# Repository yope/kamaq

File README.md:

Kamaq
=====

1. Introduction
---------------

Kamaq is a 3D-printer (FDM) controller software running on an embedded Linux
system. It is capable of controlling a RepRap-style 3D printer, but with
different electronics. Stepper motor control is done using a 8-channel (7.1)
USB audio device and some class-D audio amplifiers. Endstop switches are
monitored via GPIO inputs (interrupt-capable) and temperature control for
extruder and heated bed via standard hwmon-compatible ADC's and GPIO-outputs
for heater control. The software has a web-iterface for machine control and
monitoring. Why do it like this when there are already so many different hard-
and software projects dedicated to 3D printers (RepRap and all its
derivatives)?  Well, because as is the case with all engineers, I always know
better ;-)

2. Status of this project
-------------------------

This project is currently in heavy development. There are some bugs and missing
features, but overall the software can be (and has been) used for many
successful prints.
The software can control 4 motors (X, Y, Z and Extruder), read 3 endswitches
and control extruder- and heated-bed temperatures. The G-Code interpreter is
still very simple, but the software is already able to succesfully print
objects from a G-Code-file generated with cura or repsnapper.

3. Platform requirements
------------------------

Kamaq should be able to run on any embedded linux platform such as the beagle-
board, beagle-bone or the raspberry-pi with a suitable audio device, GPIO and
HWmon compatible A/D converters for temperature measurement.
The sound device should have twice the number of channels as the number of
motors that need to be controlled. For example a cheap 7.1 USB audio device
will be enough for controlling 4 stepper-motors.

4. Main application
-------------------

Of course the main goal for this project is controlling 3D-printer hardware,
such as the RepRap Prusa i3 for example, but it may also be adapted for other
applications requiring control of motors from G-Codes.

5. Required hardware
--------------------

5.1. Audio device
-----------------

The sound-card will work better if modified slightly, by shorting the DC-
blocking capacitors at the output. On many USB audio devices this is a
trivial task to do. For example the Sweex SC016 contains a C-Media CM6206
7.1 channel USB audio codec. Datasheets can easily be found via Google, and
they contain reference schematics that will be very similar to most
implementations of popular 7.1 USB audio devices that use this chip.
Most of the time they will use cheap through-hole electrolytic capacitors,
that are very easy to short out.

5.2. Audio amplifiers
---------------------

Bipolar 2-phase stepper-motors are best driven by a controlled current.
Although in theory, having a good model of the motor that takes into account
inductance and back-EMF at different speeds, one could calculate the correct
voltage-waveform to be applied to the motor windings and just use a voltage-
amplifier wich might be a little easier to build (specially when using class-D
amplifier IC's).
For my first hardware implementation, I built very simple class-B amplifiers
with current-feedback based on a bunch of TDA2030A I had laying around. This
version didn't require any motor modeling.
The second version which I am currently using is based on class-D audio
amplifier IC's, which save a lot of space and simplify the power supply
enormously. The class-D amplifiers lack current-feedback though, so I have
added rudimentary software support for voltage control also.

5.3. Heater control
-------------------

To control heater elements (such as for the extruder or the heated-bed of a
3D-printer), simple low-side switches with power-MOSFETS with very low-Rdson
will be perfect.
Temperature feedback is best implemented via simple A/D converters that support
HW-mon drivers, such as the ADS1015 from TI, which has mainline-linux support.

5.4. Hardware implementation
----------------------------

I have implemented all the needed hardware to control a 3D printer using this
software in very little time and effort. If there is enough interest I might
open-source the hardware (Kicad schematics and layout) too, but it is really
simple and straight-forward stuff right now hacked together in very little time.

6. Tools
--------

 * kamaq.py: Main application, starts the web-server.

 * grunner.py: This command-line tool can execude whole G-Code files or single
   movements by specifying relative distance on each axis (including extruder)
   on the command-line. It supports homing on endswitches and extruder
   temperature control. Currently not functional. Use the web-server instead.

 * set_current.py: Very simple tool that sets constant motor currents for all
   motors specified on the command-line. Can be used for adjusting motor
   current via the audio mixer. For each motor, two values are specified from
   -30000 to 30000, corresponding to the currents through each of the two
   coils. If less than 8 values (for 4 motors) are specified, the rest is
   assumed to be 0.

 * adjust_bed.sh: A script that aids in adjusting the for corners of the print-
   bed.

 * clean_extruder.sh: Move to a suitable position (high enough Z), heat
   extruder and start extruding a few cm. Deprecated. Will be removed soon
   probably.

7. TODO:
--------

Features that may or may not be implemented in the near or far future:

 * Implement pause and resume-from-layer-X.
 * Implemet G-code control via SSH or Serial port (to be able to use traditional
   printer control software).

8. Building Kamaq:
------------------

Install build dependencies (debian jessie or ubuntu):

 $ sudo apt-get install python3 cython3 libasound2-dev

Building (in-place, installation not supported yet):

 $ make

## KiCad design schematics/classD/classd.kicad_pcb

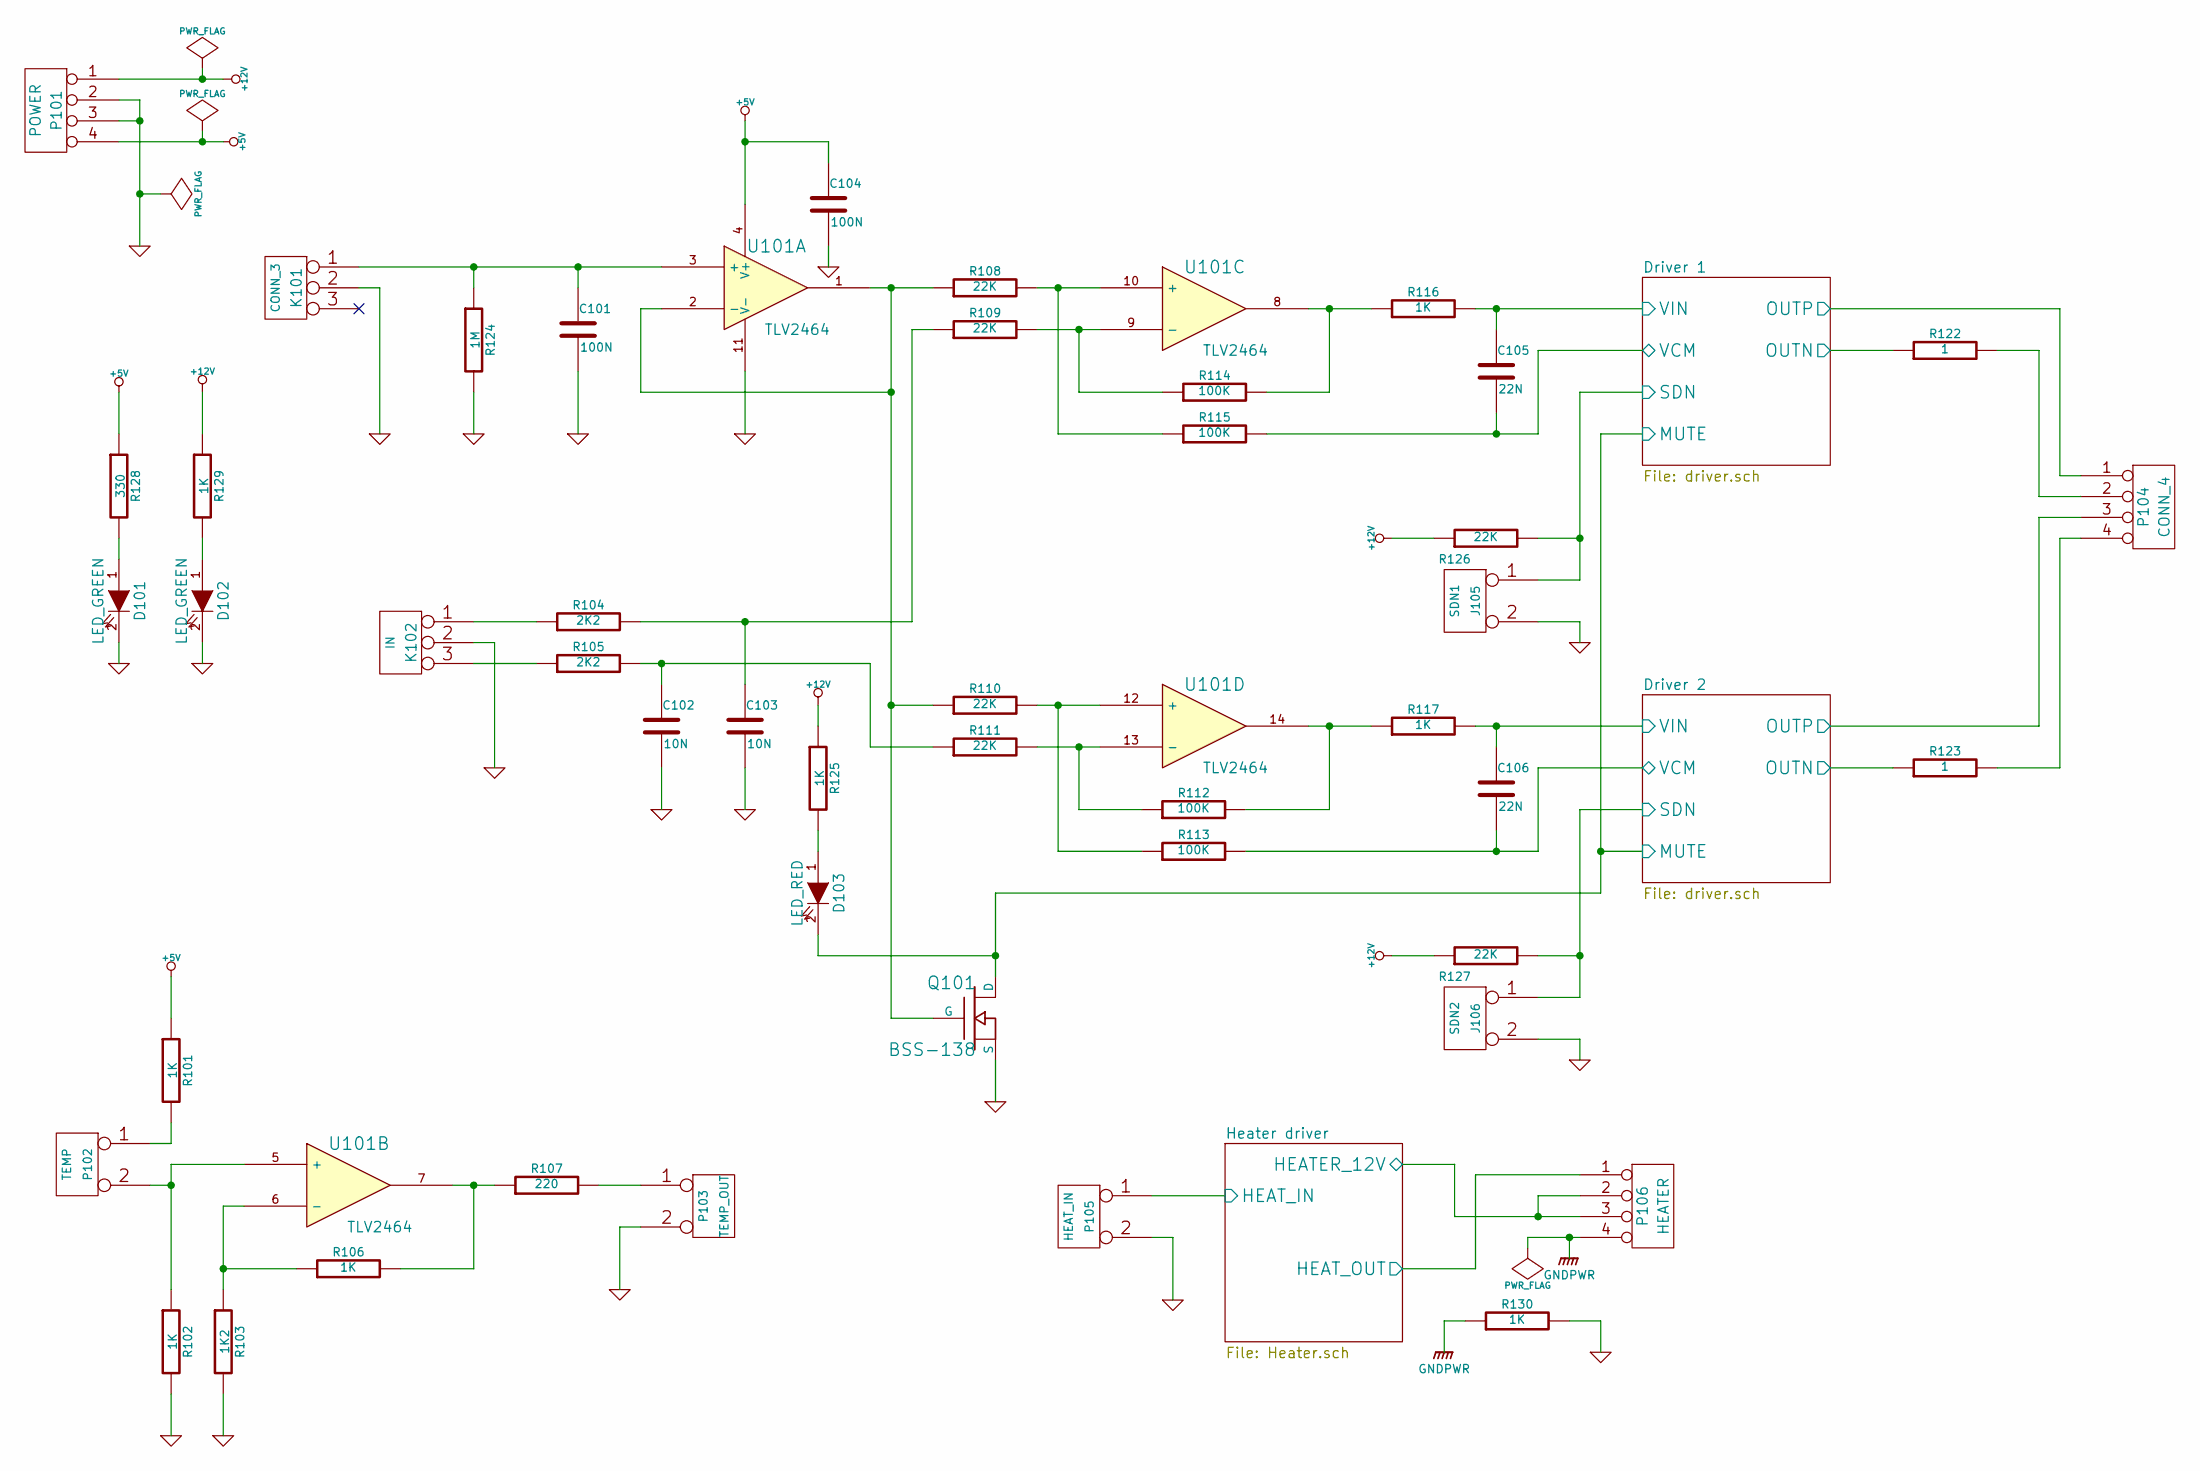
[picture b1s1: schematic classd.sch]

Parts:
C101, C104: 100N
C102, C103: 10N
C105, C106: 22N
D101, D102: LED_GREEN
D103: LED_RED
J105: SDN1
J106: SDN2
K101: CONN_3
K102: IN
P101: POWER
P102: TEMP
P103: TEMP_OUT
P104: CONN_4
P105: HEAT_IN
P106: HEATER
Q101: BSS-138
R101, R102, R106, R116, R117, R125, R129, R130: 1K
R103: 1K2
R104, R105: 2K2
R107: 220
R108, R109, R110, R111, R126, R127: 22K
R112, R113, R114, R115: 100K
R122, R123: 1
R124: 1M
R128: 330
U101: TLV2464

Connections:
+5V: C104.1, P101.4, R101.1, R128.1, U101.4 (V+); also elsewhere on the board
+12V: P101.1, R125.1, R126.1, R127.1, R129.1; also elsewhere on the board
/Driver 1/MUTE: D103.2 (K), Q101.D; also elsewhere on the board
/Driver 1/OUTN: R122.1; also elsewhere on the board
/Driver 1/OUTP: P104.1; also elsewhere on the board
/Driver 1/SDN: J105.1, R126.2; also elsewhere on the board
/Driver 1/VCM: C105.2, R115.2; also elsewhere on the board
/Driver 1/VIN: C105.1, R116.2; also elsewhere on the board
/Driver 2/OUTN: R123.1; also elsewhere on the board
/Driver 2/OUTP: P104.3; also elsewhere on the board
/Driver 2/SDN: J106.1, R127.2; also elsewhere on the board
/Driver 2/VCM: C106.2, R113.2; also elsewhere on the board
/Driver 2/VIN: C106.1, R117.2; also elsewhere on the board
/Heater driver/HEATER_12V: P106.2, P106.3; also elsewhere on the board
/Heater driver/HEAT_IN: P105.1; also elsewhere on the board
/Heater driver/HEAT_OUT: P106.1; also elsewhere on the board
GND: C101.2, C102.2, C103.2, C104.2, D101.2 (K), D102.2 (K), J105.2 (PM), J106.2 (PM), K101.2 (PM), K102.2 (PM), P101.2, P101.3, P103.2 (PM), P105.2 (PM), Q101.S, R102.2, R103.2, R124.2, R130.2, U101.11 (V-); also elsewhere on the board
GNDPWR: P106.4, R130.1; also elsewhere on the board
unnamed: P102.2 (PM), R102.1, U101.5 (+)
unnamed: P103.1, R107.2
unnamed: R106.2, R107.1, U101.7
unnamed: R103.1, R106.1, U101.6 (-)
unnamed: P102.1, R101.2
unnamed: D101.1 (A), R128.2
unnamed: D102.1 (A), R129.2
unnamed: D103.1 (A), R125.2
unnamed: R114.2, R116.1, U101.8
unnamed: Q101.G, R108.1, R110.1, U101.1, U101.2 (-)
unnamed: R109.2, R114.1, U101.9 (-)
unnamed: C103.1, R104.2, R109.1
unnamed: R108.2, R115.1, U101.10 (+)
unnamed: P104.4, R123.2
unnamed: P104.2, R122.2
unnamed: K102.3, R105.1
unnamed: C102.1, R105.2, R111.1
unnamed: K102.1, R104.1
unnamed: C101.1, K101.1, R124.1, U101.3 (+)
unnamed: R112.2, R117.1, U101.14
unnamed: R110.2, R113.1, U101.12 (+)
unnamed: R111.2, R112.1, U101.13 (-)

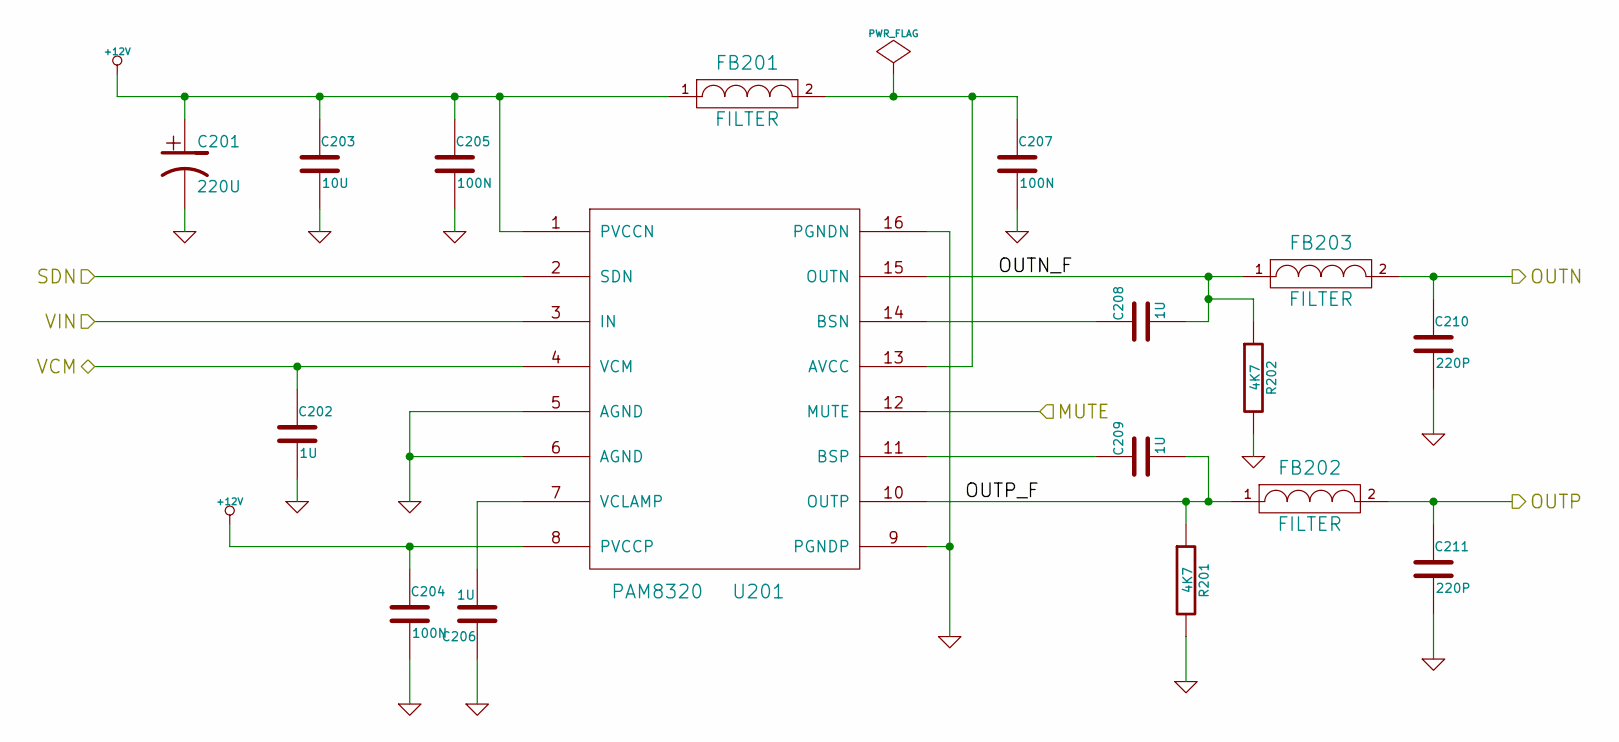
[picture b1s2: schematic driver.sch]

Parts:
C201: 220U
C202, C206, C208, C209: 1U
C203: 10U
C204, C205, C207: 100N
C210, C211: 220P
FB201, FB202, FB203: FILTER
R201, R202: 4K7
U201: PAM8320

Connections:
+12V: C201.1, C203.1, C204.1, C205.1, FB201.1, U201.1 (PVCCN), U201.8 (PVCCP); also elsewhere on the board
/Driver 1/MUTE: U201.12 (MUTE); also elsewhere on the board
/Driver 1/OUTN: C210.1, FB203.2; also elsewhere on the board
/Driver 1/OUTN_F: C208.2, FB203.1, R202.1, U201.15 (OUTN)
/Driver 1/OUTP: C211.1, FB202.2; also elsewhere on the board
/Driver 1/OUTP_F: C209.2, FB202.1, R201.1, U201.10 (OUTP)
/Driver 1/SDN: U201.2 (SDN); also elsewhere on the board
/Driver 1/VCM: C202.1, U201.4 (VCM); also elsewhere on the board
/Driver 1/VIN: U201.3 (IN); also elsewhere on the board
GND: C201.2, C202.2, C203.2, C204.2, C205.2, C206.1, C207.2, C210.2, C211.2, R201.2, R202.2, U201.5 (AGND), U201.6 (AGND), U201.9 (PGNDP), U201.16 (PGNDN); also elsewhere on the board
unnamed: C206.2, U201.7 (VCLAMP)
unnamed: C207.1, FB201.2, U201.13 (AVCC)
unnamed: C209.1, U201.11 (BSP)
unnamed: C208.1, U201.14 (BSN)

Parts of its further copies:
C301: 220U
C302, C306, C308, C309: 1U
C303: 10U
C304, C305, C307: 100N
C310, C311: 220P
FB301, FB302, FB303: FILTER
R301, R302: 4K7
U301: PAM8320

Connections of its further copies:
+12V: C301.1, C303.1, C304.1, C305.1, FB301.1, U301.1 (PVCCN), U301.8 (PVCCP); also elsewhere on the board
/Driver 1/MUTE: U301.12 (MUTE); also elsewhere on the board
/Driver 2/OUTN: C310.1, FB303.2; also elsewhere on the board
/Driver 2/OUTN_F: C308.2, FB303.1, R302.1, U301.15 (OUTN)
/Driver 2/OUTP: C311.1, FB302.2; also elsewhere on the board
/Driver 2/OUTP_F: C309.2, FB302.1, R301.1, U301.10 (OUTP)
/Driver 2/SDN: U301.2 (SDN); also elsewhere on the board
/Driver 2/VCM: C302.1, U301.4 (VCM); also elsewhere on the board
/Driver 2/VIN: U301.3 (IN); also elsewhere on the board
GND: C301.2, C302.2, C303.2, C304.2, C305.2, C306.1, C307.2, C310.2, C311.2, R301.2, R302.2, U301.5 (AGND), U301.6 (AGND), U301.9 (PGNDP), U301.16 (PGNDN); also elsewhere on the board
unnamed: C306.2, U301.7 (VCLAMP)
unnamed: C307.1, FB301.2, U301.13 (AVCC)
unnamed: C309.1, U301.11 (BSP)
unnamed: C308.1, U301.14 (BSN)

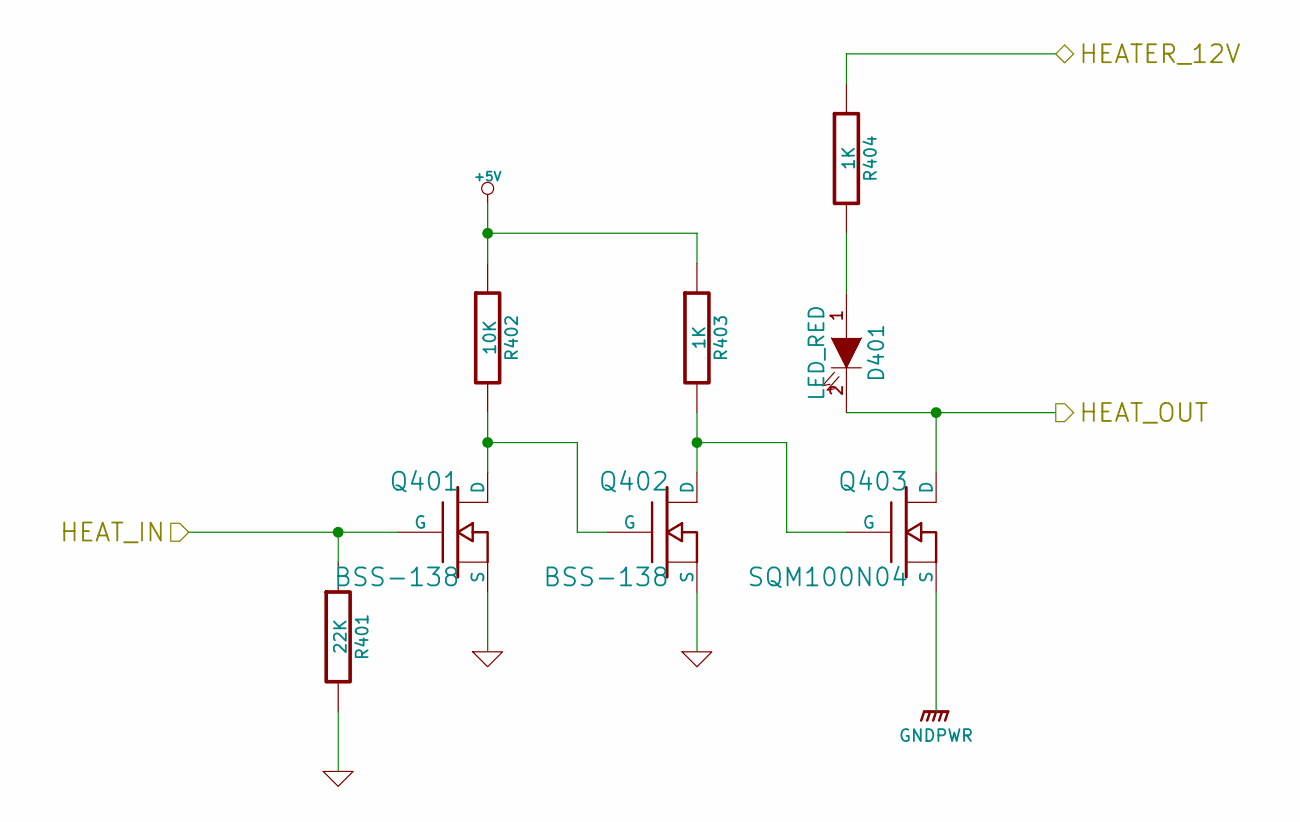
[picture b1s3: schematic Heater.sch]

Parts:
D401: LED_RED
Q401, Q402: BSS-138
Q403: SQM100N04
R401: 22K
R402: 10K
R403, R404: 1K

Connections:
+5V: R402.1, R403.1; also elsewhere on the board
/Heater driver/HEATER_12V: R404.1; also elsewhere on the board
/Heater driver/HEAT_IN: Q401.G, R401.1; also elsewhere on the board
/Heater driver/HEAT_OUT: D401.2 (K), Q403.2 (D); also elsewhere on the board
GND: Q401.S, Q402.S, R401.2; also elsewhere on the board
GNDPWR: Q403.3 (S); also elsewhere on the board
unnamed: Q402.D, Q403.1 (G), R403.2
unnamed: Q401.D, Q402.G, R402.2
unnamed: D401.1 (A), R404.2

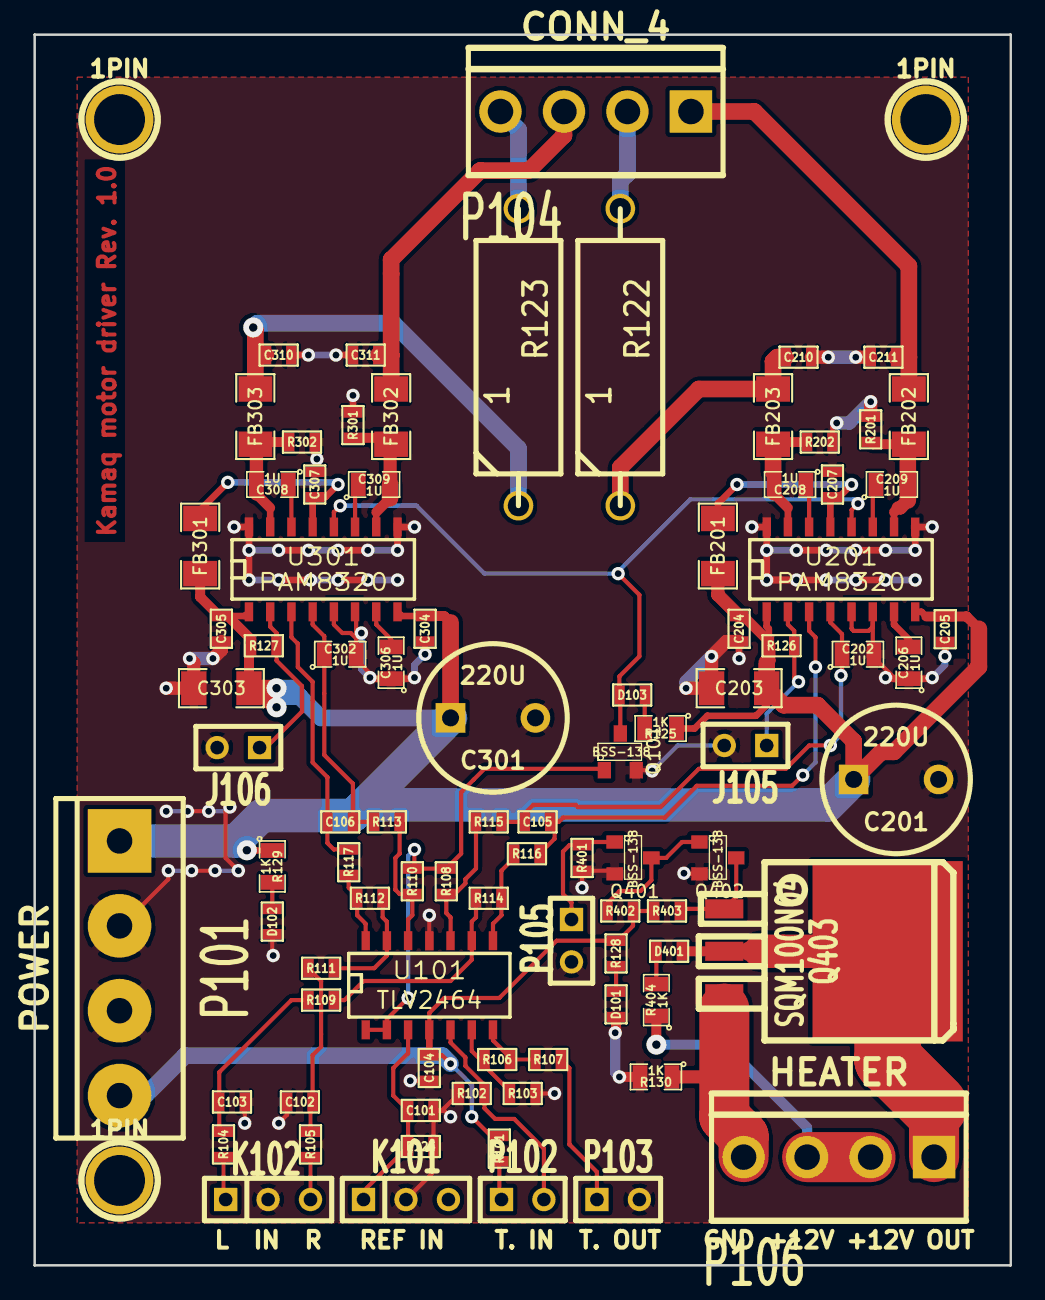
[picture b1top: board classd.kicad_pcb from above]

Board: 2 copper layers, 58.4 x 73.7 mm, 92 parts (0 on the bottom side), 55 nets.

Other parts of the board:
1PIN, 1PIN#2, 1PIN#3: P***; 1pin

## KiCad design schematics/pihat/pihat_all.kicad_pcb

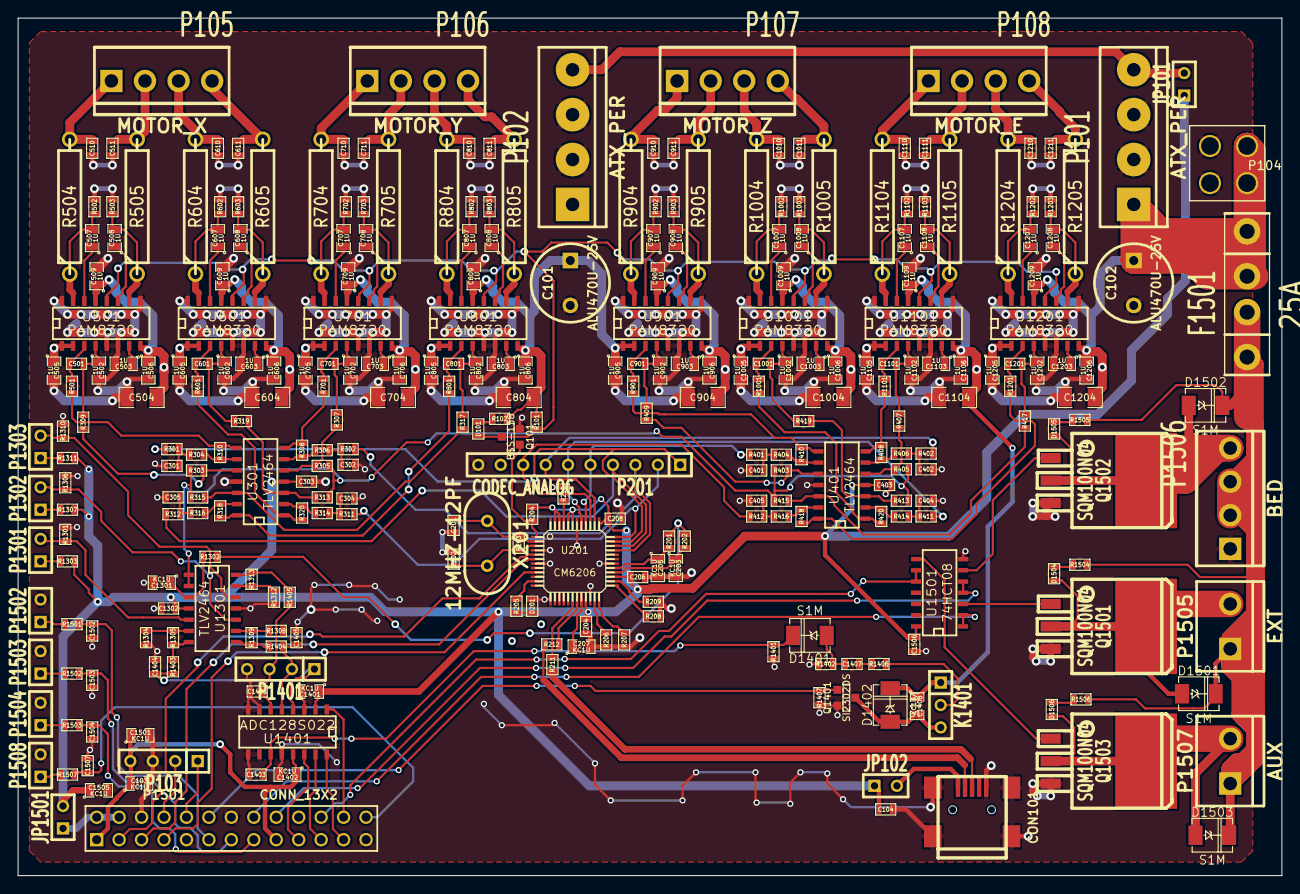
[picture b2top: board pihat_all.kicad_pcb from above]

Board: 2 copper layers, 143.0 x 97.0 mm, 305 parts (0 on the bottom side), 192 nets.

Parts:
C101, C102: ALU470U-25V; C2V8
C103, C203, C205, C207, C1301, C1401, C1402, C1408, C1501, C1505: KC1U; SM0805
C104: KC10U; SM0603
C201, C202, C204, C206, C208, C303, C403, C1302, C1403, C1502, C1503, C1504, C1506, C1507: 100N; SM0603
C301, C302, C304, C305, C401, C402, C404, C405, C501, C601, C701, C801, C901, C1001, C1101, C1201, C1404, C1405, C1406, C1407: 10N; SM0603
C502, C503, C505, C506, C507, C508, C509, C602, C603, C605, C606, C607, C608, C609, C702, C703, C705, C706, C707, C708, C709, C802, C803, C805, C806, C807, C808, C809, C902, C903, C905, C906, C907, C908, C909, C1002, C1003, C1005, C1006, C1007, C1008, C1009, C1102, C1103, C1105, C1106, C1107, C1108, C1109, C1202, C1203, C1205, C1206, C1207, C1208, C1209: 1U; SM0805
C504, C604, C704, C804, C904, C1004, C1104, C1204: 10U; SM1206
C510, C511, C610, C611, C710, C711, C810, C811, C910, C911, C1010, C1011, C1110, C1111, C1210, C1211: 220P; SM0603
CON101: USB-MINI-B; USB_MINI_B
D101, D201, D1504, D1505, D1506: LED; SM0603
D1401, D1402, D1501, D1502, D1503: S1M; DO-214AC(SMA)
F1501: 25A; ATO257
JP101, JP102, JP1501: JUMPER; SIL-2
K1401: FAN; SIL-3
P101, P102: ATX_PER; bornier4
P103: SERIAL; SIL-4
P104: MOLEX-39-28-1043; MINIFIT-4
P105: MOTOR_X; MC4
P106: MOTOR_Y; MC4
P107: MOTOR_Z; MC4
P108: MOTOR_E; MC4
P201: CODEC_ANALOG; SIL-10
P1301: TEMP_EXT; SIL-2
P1302: TEMP_BED; SIL-2
P1303: TEMP_AUX; SIL-2
P1401: TEMP_ADC; SIL-4
P1501: CONN_13X2; pin_array_13x2
P1502: END_X; SIL-2
P1503: END_Y; SIL-2
P1504: END_Z; SIL-2
P1505: EXT; bornier2
P1506: BED; MC4
P1507: AUX; bornier2
P1508: END_L; SIL-2
Q101: BSS-138; SOT23GDS
Q1401: SI2302DS; SOT23GDS
Q1501, Q1502, Q1503: SQM100N04; TO263
R101, R102, R1301, R1302, R1303, R1305, R1306, R1307, R1309, R1310, R1311, R1313, R1402, R1406, R1501, R1502, R1503, R1504, R1505, R1506, R1507: 1K; SM0603
R201: N.P.; SM0603
R202: 0; SM0603
R203: 1M; SM0603
R204, R303, R304, R305, R306, R313, R314, R315, R316, R403, R404, R405, R406, R413, R414, R415, R416, R1401, R1407: 22K; SM0603
R205: 330; SM0603
R206, R207, R208, R209, R210, R307, R308, R309, R310, R317, R318, R319, R320, R407, R408, R409, R410, R417, R418, R419, R420: 10K; SM0603
R211, R212: 22; SM0603
R301, R302, R311, R312, R401, R402, R411, R412, R501, R601, R701, R801, R901, R1001, R1101, R1201: 2.2K; SM0603
R502, R503, R602, R603, R702, R703, R802, R803, R902, R903, R1002, R1003, R1102, R1103, R1202, R1203: 47K; SM0603
R504, R505, R604, R605, R704, R705, R804, R805, R904, R905, R1004, R1005, R1104, R1105, R1204, R1205: 0.5/3W; R6
R1304, R1308, R1312: 1.2K; SM0603
R1403, R1404, R1405: 47; SM0603
U201: CM6206; AB2_LQFP48
U301, U401, U1301: TLV2464; SO14E
U501, U601, U701, U801, U901, U1001, U1101, U1201: PAM8320; SO16E
U1401: ADC128S022; SO16E
U1501: 74HCT08; SO14E
X201: 12MHZ-12PF; HC-49V

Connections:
+3.3V: C103.1, C1402.1, C1501.1, P103.4, P1501.1, P1501.17, U1401.13
+5V: C104.1, C204.1, C206.1, C208.1, C303.1, C403.1, C1302.1, C1401.1, C1505.1, C1506.1, JP101.1, JP102.1, JP1501.2, R204.1, R1303.1, R1307.1, R1311.1, U201.21, U201.27, U201.37, U201.43, U201.44, U201.46, U201.47, U301.4, U401.4, U1301.4, U1401.2, U1501.14
+12V: C101.1, C102.1, C504.1, C505.1, C506.1, C509.1, C604.1, C605.1, C606.1, C609.1, C704.1, C705.1, C706.1, C709.1, C804.1, C805.1, C806.1, C809.1, C904.1, C905.1, C906.1, C909.1, C1004.1, C1005.1, C1006.1, C1009.1, C1104.1, C1105.1, C1106.1, C1109.1, C1204.1, C1205.1, C1206.1, C1209.1, C1408.1, D1402.2, F1501.1, K1401.1, P101.1, P102.1, P104.3, P104.4, R101.1, R102.1, U501.1, U501.2, U501.8, U501.13, U601.1, U601.2, U601.8, U601.13, U701.1, U701.2, U701.8, U701.13, U801.1, U801.2, U801.8, U801.13, U901.1, U901.2, U901.8, U901.13, U1001.1, U1001.2, U1001.8, U1001.13, U1101.1, U1101.2, U1101.8, U1101.13, U1201.1, U1201.2, U1201.8, U1201.13
/ADC/FAN_PWM: P1501.12, Q1401.G, R1407.1
/ADC/SPI_MISO: P1501.21, U1401.15
/ADC/SPI_MOSI: P1501.19, U1401.14
/ADC/SPI_SCLK: P1501.23, U1401.16
/ADC/TEMP_AUX: R1313.2, R1405.2, U1301.14
/ADC/TEMP_BED: R1309.2, R1404.2, U1301.8
/ADC/TEMP_EXT: R1305.2, R1403.2, U1301.7
/Audio Codec/CODEC_VBIAS: C205.1, R201.2, U201.29
/Audio Codec/CODEC_VREF: C203.1, R202.2, U201.28
/Audio Codec/MINT: P1501.7, U201.9
/Audio Codec/PDSW: Q101.G, R204.2, U201.1
/Audio Codec/SCL: P1501.5, U201.6
/Audio Codec/SDA: P1501.3, U201.5
/Audio Codec/USB_DM: CON101.2, R212.1
/Audio Codec/USB_DP: CON101.3, R211.1
/Audio Codec/VBIAS: R201.1, R202.1, R1302.1
/Biasing1/IN_A: P201.1, R301.1, U201.35
/Biasing1/IN_B: P201.2, R311.1, U201.36
/Biasing1/IN_C: P201.3, R302.1, U201.33
/Biasing1/IN_D: P201.4, R312.1, U201.34
/Biasing2/IN_A: P201.5, R401.1, U201.40
/Biasing2/IN_B: P201.6, R411.1, U201.41
/Biasing2/IN_C: P201.7, R402.1, U201.38
/Biasing2/IN_D: P201.8, R412.1, U201.39
/GPIO/GPIO7: C1507.1, P1501.26, R1507.1
/GPIO/GPIO17: C1502.1, P1501.11, R1501.1
/GPIO/GPIO22: C1504.1, P1501.15, R1503.1
/GPIO/GPIO23: P1501.16, U1501.1, U1501.2
/GPIO/GPIO24: P1501.18, U1501.4, U1501.5
/GPIO/GPIO25: P1501.22, U1501.9, U1501.10
/GPIO/GPIO27: C1503.1, P1501.13, R1502.1
/GPIO/SPI_nCE0: P1501.24, U1401.1
/GPIO/UART_RXD: P103.1, P1501.10
/GPIO/UART_TXD: P103.2, P1501.8
/Power Amp 1/OUTN: C510.1, P105.1, R504.2
/Power Amp 1/OUTP: C511.1, P105.2, R505.2
/Power Amp 1/VCM: C501.2, C502.1, R309.2, U501.4
/Power Amp 1/VIN: R310.2, R501.1, U301.8
/Power Amp 2/OUTN: C610.1, P105.3, R604.2
/Power Amp 2/OUTP: C611.1, P105.4, R605.2
/Power Amp 2/VCM: C601.2, C602.1, R319.2, U601.4
/Power Amp 2/VIN: R320.2, R601.1, U301.1
/Power Amp 3/OUTN: C710.1, P106.1, R704.2
/Power Amp 3/OUTP: C711.1, P106.2, R705.2
/Power Amp 3/VCM: C701.2, C702.1, R307.2, U701.4
/Power Amp 3/VIN: R308.2, R701.1, U301.7
/Power Amp 4/OUTN: C810.1, P106.3, R804.2
/Power Amp 4/OUTP: C811.1, P106.4, R805.2
/Power Amp 4/VCM: C801.2, C802.1, R317.2, U801.4
/Power Amp 4/VIN: R318.2, R801.1, U301.14
/Power Amp 5/OUTN: C910.1, P107.1, R904.2
/Power Amp 5/OUTP: C911.1, P107.2, R905.2
/Power Amp 5/VCM: C901.2, C902.1, R409.2, U901.4
/Power Amp 5/VIN: R410.2, R901.1, U401.8
/Power Amp 6/OUTN: C1010.1, P107.3, R1004.2
/Power Amp 6/OUTP: C1011.1, P107.4, R1005.2
/Power Amp 6/VCM: C1001.2, C1002.1, R419.2, U1001.4
/Power Amp 6/VIN: R420.2, R1001.1, U401.1
/Power Amp 7/OUTN: C1110.1, P108.1, R1104.2
/Power Amp 7/OUTP: C1111.1, P108.2, R1105.2
/Power Amp 7/VCM: C1101.2, C1102.1, R407.2, U1101.4
/Power Amp 7/VIN: R408.2, R1101.1, U401.7
/Power Amp 8/OUTN: C1210.1, P108.3, R1204.2
/Power Amp 8/OUTP: C1211.1, P108.4, R1205.2
/Power Amp 8/VCM: C1201.2, C1202.1, R417.2, U1201.4
/Power Amp 8/VIN: R418.2, R1201.1, U401.14
GND: C101.2, C102.2, C103.2, C104.2, C201.2, C202.2, C203.2, C204.2, C205.2, C206.2, C207.2, C208.2, C301.2, C302.2, C303.2, C304.2, C305.2, C401.2, C402.2, C403.2, C404.2, C405.2, C502.2, C503.2, C504.2, C505.2, C506.2, C509.2, C510.2, C511.2, C602.2, C603.2, C604.2, C605.2, C606.2, C609.2, C610.2, C611.2, C702.2, C703.2, C704.2, C705.2, C706.2, C709.2, C710.2, C711.2, C802.2, C803.2, C804.2, C805.2, C806.2, C809.2, C810.2, C811.2, C902.2, C903.2, C904.2, C905.2, C906.2, C909.2, C910.2, C911.2, C1002.2, C1003.2, C1004.2, C1005.2, C1006.2, C1009.2, C1010.2, C1011.2, C1102.2, C1103.2, C1104.2, C1105.2, C1106.2, C1109.2, C1110.2, C1111.2, C1202.2, C1203.2, C1204.2, C1205.2, C1206.2, C1209.2, C1210.2, C1211.2, C1301.2, C1302.2, C1401.2, C1402.2, C1403.2, C1404.2, C1405.2, C1406.2, C1501.2, C1502.2, C1503.2, C1504.2, C1505.2, C1506.2, C1507.2, CON101.5, CON101.6, CON101.7, CON101.8, CON101.9, D201.2, P101.2, P101.3, P102.2, P102.3, P103.3, P104.1, P104.2, P201.10, P1401.4, P1501.6, P1501.9, P1501.14, P1501.20, P1501.25, P1502.2, P1503.2, P1504.2, P1506.1, P1508.2, Q101.S, Q1401.S, Q1501.3, Q1502.3, Q1503.3, R206.2, R207.2, R208.2, R209.2, R210.2, R502.2, R503.2, R602.2, R603.2, R702.2, R703.2, R802.2, R803.2, R902.2, R903.2, R1002.2, R1003.2, R1102.2, R1103.2, R1202.2, R1203.2, R1301.2, R1304.2, R1306.2, R1308.2, R1310.2, R1312.2, R1401.1, R1402.2, R1407.2, U201.4, U201.7, U201.13, U201.22, U201.30, U201.42, U301.11, U401.11, U501.5, U501.6, U501.9, U501.16, U601.5, U601.6, U601.9, U601.16, U701.5, U701.6, U701.9, U701.16, U801.5, U801.6, U801.9, U801.16, U901.5, U901.6, U901.9, U901.16, U1001.5, U1001.6, U1001.9, U1001.16, U1101.5, U1101.6, U1101.9, U1101.16, U1201.5, U1201.6, U1201.9, U1201.16, U1301.11, U1401.3, U1401.7, U1401.8, U1401.9, U1401.10, U1401.12, U1501.7
MUTE: D101.2, Q101.D, R101.2, U501.12, U601.12, U701.12, U801.12, U901.12, U1001.12, U1101.12, U1201.12
unnamed: CON101.1, JP102.2
unnamed: JP101.2, P101.4, P102.4
unnamed: D101.1, R102.2
unnamed: C201.1, R203.1, U201.2, X201.1
unnamed: C207.1, U201.20
unnamed: R210.1, U201.45
unnamed: R209.1, U201.26
unnamed: R208.1, U201.25
unnamed: R207.1, U201.24
unnamed: C202.1, R203.2, U201.3, X201.2
unnamed: R206.1, U201.23
unnamed: R211.2, U201.18
unnamed: R212.2, U201.19
unnamed: D201.1, R205.2
unnamed: R205.1, U201.11
unnamed: R313.2, R319.1, U301.3
unnamed: R315.2, R317.1, U301.12
unnamed: C301.1, R301.2, R304.1
unnamed: C305.1, R312.2, R316.1
unnamed: C304.1, R311.2, R314.1
unnamed: R304.2, R310.1, U301.9
unnamed: R316.2, R318.1, U301.13
unnamed: R306.2, R308.1, U301.6
unnamed: R314.2, R320.1, U301.2
unnamed: R303.2, R309.1, U301.10
unnamed: R305.2, R307.1, U301.5
unnamed: C302.1, R302.2, R306.1
unnamed: R413.2, R419.1, U401.3
unnamed: R415.2, R417.1, U401.12
unnamed: C401.1, R401.2, R404.1
unnamed: C405.1, R412.2, R416.1
unnamed: C404.1, R411.2, R414.1
unnamed: R404.2, R410.1, U401.9
unnamed: R416.2, R418.1, U401.13
unnamed: R406.2, R408.1, U401.6
unnamed: R414.2, R420.1, U401.2
unnamed: R403.2, R409.1, U401.10
unnamed: R405.2, R407.1, U401.5
unnamed: C402.1, R402.2, R406.1
unnamed: C501.1, R501.2, U501.3
unnamed: C503.1, U501.7
unnamed: C508.2, R503.1, R505.1, U501.10
unnamed: C507.1, U501.14
unnamed: C508.1, U501.11
unnamed: C507.2, R502.1, R504.1, U501.15
unnamed: C603.1, U601.7
unnamed: C601.1, R601.2, U601.3
unnamed: C608.2, R603.1, R605.1, U601.10
unnamed: C607.1, U601.14
unnamed: C608.1, U601.11
unnamed: C607.2, R602.1, R604.1, U601.15
unnamed: C703.1, U701.7
unnamed: C701.1, R701.2, U701.3
unnamed: C708.2, R703.1, R705.1, U701.10
unnamed: C707.1, U701.14
unnamed: C708.1, U701.11
unnamed: C707.2, R702.1, R704.1, U701.15
unnamed: C803.1, U801.7
unnamed: C801.1, R801.2, U801.3
unnamed: C807.2, R802.1, R804.1, U801.15
unnamed: C807.1, U801.14
unnamed: C808.2, R803.1, R805.1, U801.10
unnamed: C808.1, U801.11
unnamed: C903.1, U901.7
unnamed: C901.1, R901.2, U901.3
unnamed: C907.2, R902.1, R904.1, U901.15
unnamed: C907.1, U901.14
unnamed: C908.2, R903.1, R905.1, U901.10
unnamed: C908.1, U901.11
unnamed: C1003.1, U1001.7
unnamed: C1001.1, R1001.2, U1001.3
unnamed: C1007.2, R1002.1, R1004.1, U1001.15
unnamed: C1007.1, U1001.14
unnamed: C1008.2, R1003.1, R1005.1, U1001.10
unnamed: C1008.1, U1001.11
unnamed: C1103.1, U1101.7
unnamed: C1101.1, R1101.2, U1101.3
unnamed: C1108.2, R1103.1, R1105.1, U1101.10
unnamed: C1107.1, U1101.14
unnamed: C1108.1, U1101.11
unnamed: C1107.2, R1102.1, R1104.1, U1101.15
unnamed: C1203.1, U1201.7
unnamed: C1201.1, R1201.2, U1201.3
unnamed: C1208.2, R1203.1, R1205.1, U1201.10
unnamed: C1207.1, U1201.14
unnamed: C1208.1, U1201.11
unnamed: C1207.2, R1202.1, R1204.1, U1201.15
unnamed: R1312.1, R1313.1, U1301.13
unnamed: P1303.2, R1310.1, U1301.12
unnamed: P1303.1, R1311.2
unnamed: P1302.1, R1307.2
unnamed: P1302.2, R1306.1, U1301.10
unnamed: R1308.1, R1309.1, U1301.9
unnamed: C1301.1, R1302.2, U1301.3
unnamed: R1304.1, R1305.1, U1301.6
unnamed: P1301.2, R1301.1, U1301.5
unnamed: P1301.1, R1303.2
unnamed: C1403.1, D1401.2, R1401.2, U1401.11
unnamed: C1407.1, D1401.1, R1402.1
unnamed: C1407.2, R1406.1
unnamed: K1401.2, R1406.2
unnamed: C1408.2, D1402.1, K1401.3, Q1401.D
unnamed: C1406.1, P1401.3, R1405.1, U1401.6
unnamed: C1405.1, P1401.2, R1404.1, U1401.5
unnamed: C1404.1, P1401.1, R1403.1, U1401.4
unnamed: D1506.1, R1506.2
unnamed: D1503.1, D1506.2, P1507.2, Q1503.2
unnamed: P1504.1, R1503.2
unnamed: P1503.1, R1502.2
unnamed: P1502.1, R1501.2
unnamed: D1501.1, D1504.2, P1505.2, Q1501.2
unnamed: D1502.1, D1505.2, P1506.4, Q1502.2
unnamed: D1505.1, R1505.2
unnamed: D1504.1, R1504.2
unnamed: D1501.2, D1502.2, D1503.2, F1501.2, P1505.1, P1506.2, P1506.3, P1507.1, R1504.1, R1505.1, R1506.1
unnamed: P1508.1, R1507.2
unnamed: JP1501.1, P1501.2, P1501.4
unnamed: Q1502.1, U1501.6
unnamed: Q1503.1, U1501.8
unnamed: Q1501.1, U1501.3
VBIAS: R303.1, R305.1, R313.1, R315.1, R403.1, R405.1, R413.1, R415.1, U1301.1, U1301.2
